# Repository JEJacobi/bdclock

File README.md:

# Birth/Death Clock
A circuit that blinks for every averaged birth and death (inspired by xkcd's 'Frequency').

This was a simple circuit I made about a year ago to learn about EAGLE's workflow and
PCB design. All credit for inspiration goes to [xkcd](https://xkcd.com/1331/).

The 'birth' LED blinks at about 4.16 Hz, 14980/hr or 131 million/year.

The 'death' LED blinks at about 1.78 Hz, 6408/hr or 56.13 million/year.

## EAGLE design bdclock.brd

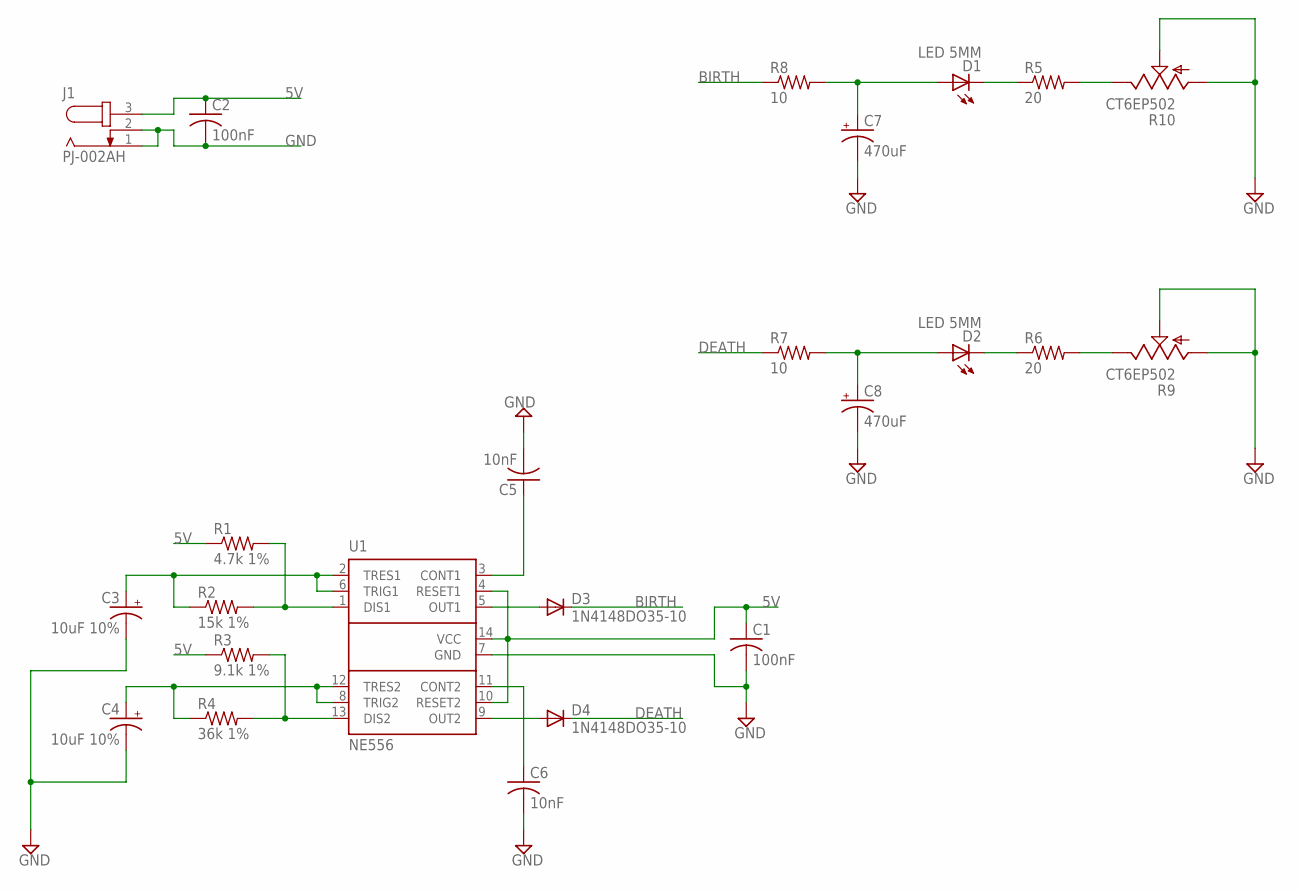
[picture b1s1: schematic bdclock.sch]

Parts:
C1, C2: 100nF; C025-025X050
C3, C4: 10uF 10%; E2-5
C5, C6: 10nF; C025-024X044
C7, C8: 470uF; E2,5-6
D1, D2: LED 5MM; LED5MM
D3, D4: 1N4148DO35-10; DO35-10
J1: PJ-002AH; SPC4077
R1: 4.7k 1%; 0207/10
R2: 15k 1%; 0207/10
R3: 9.1k 1%; 0207/10
R4: 36k 1%; 0207/10
R5, R6: 20; 0207/10
R7, R8: 10; 0207/10
R9, R10: CT6EP502; CT6
U1: NE556; DIL14

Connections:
5V: C1.1, C2.1, J1.3, R1.1, R3.1, U1.4 (RESET1), U1.10 (RESET2), U1.14 (VCC)
BIRTH: D3.C, R8.1
DEATH: D4.C, R7.1
GND: C1.2, C2.2, C3.-, C4.-, C5.2, C6.2, C7.-, C8.-, J1.1, J1.2, R9.A, R9.S, R10.A, R10.S, U1.7 (GND)
unnamed: C3.+, R2.1, U1.2 (TRES1), U1.6 (TRIG1)
unnamed: D3.A, U1.5 (OUT1)
unnamed: C7.+, D1.A, R8.2
unnamed: C8.+, D2.A, R7.2
unnamed: R5.2, R10.E
unnamed: R6.2, R9.E
unnamed: D2.K (C), R6.1
unnamed: D1.K (C), R5.1
unnamed: D4.A, U1.9 (OUT2)
unnamed: R1.2, R2.2, U1.1 (DIS1)
unnamed: C4.+, R4.1, U1.8 (TRIG2), U1.12 (TRES2)
unnamed: C6.1, U1.11 (CONT2)
unnamed: C5.1, U1.3 (CONT1)
unnamed: R3.2, R4.2, U1.13 (DIS2)

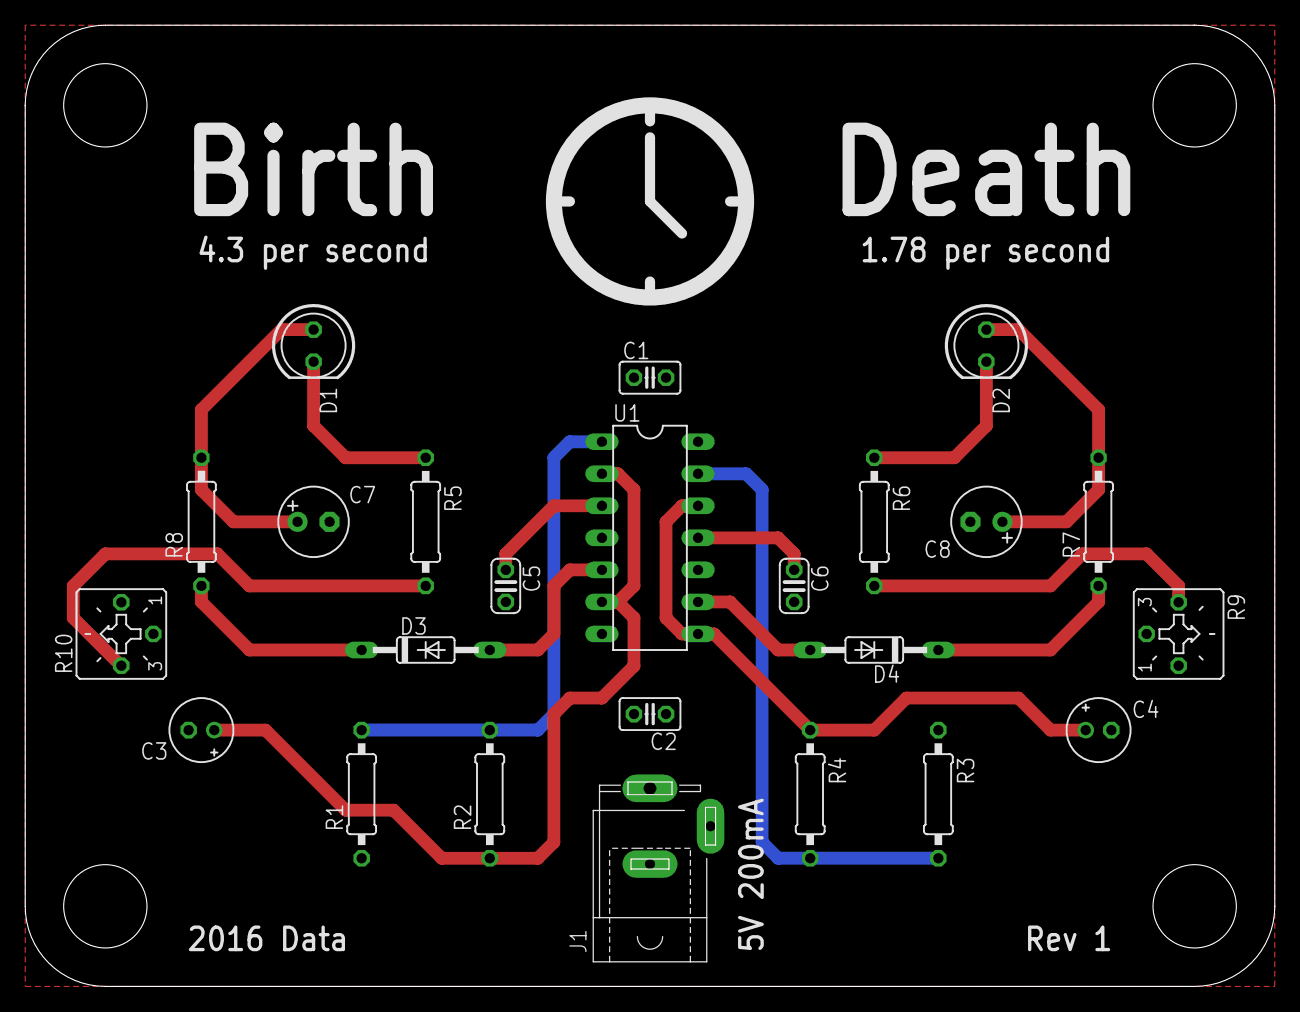
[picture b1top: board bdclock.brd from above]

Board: 2 copper layers, 99.1 x 76.2 mm, 24 parts (0 on the bottom side), 18 nets.

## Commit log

2016-09-26 Initial complete rev 1 commit from a few months back.
